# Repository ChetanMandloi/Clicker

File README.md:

# Clicker
PCB schematics, ESP code, User side programs for the clicker

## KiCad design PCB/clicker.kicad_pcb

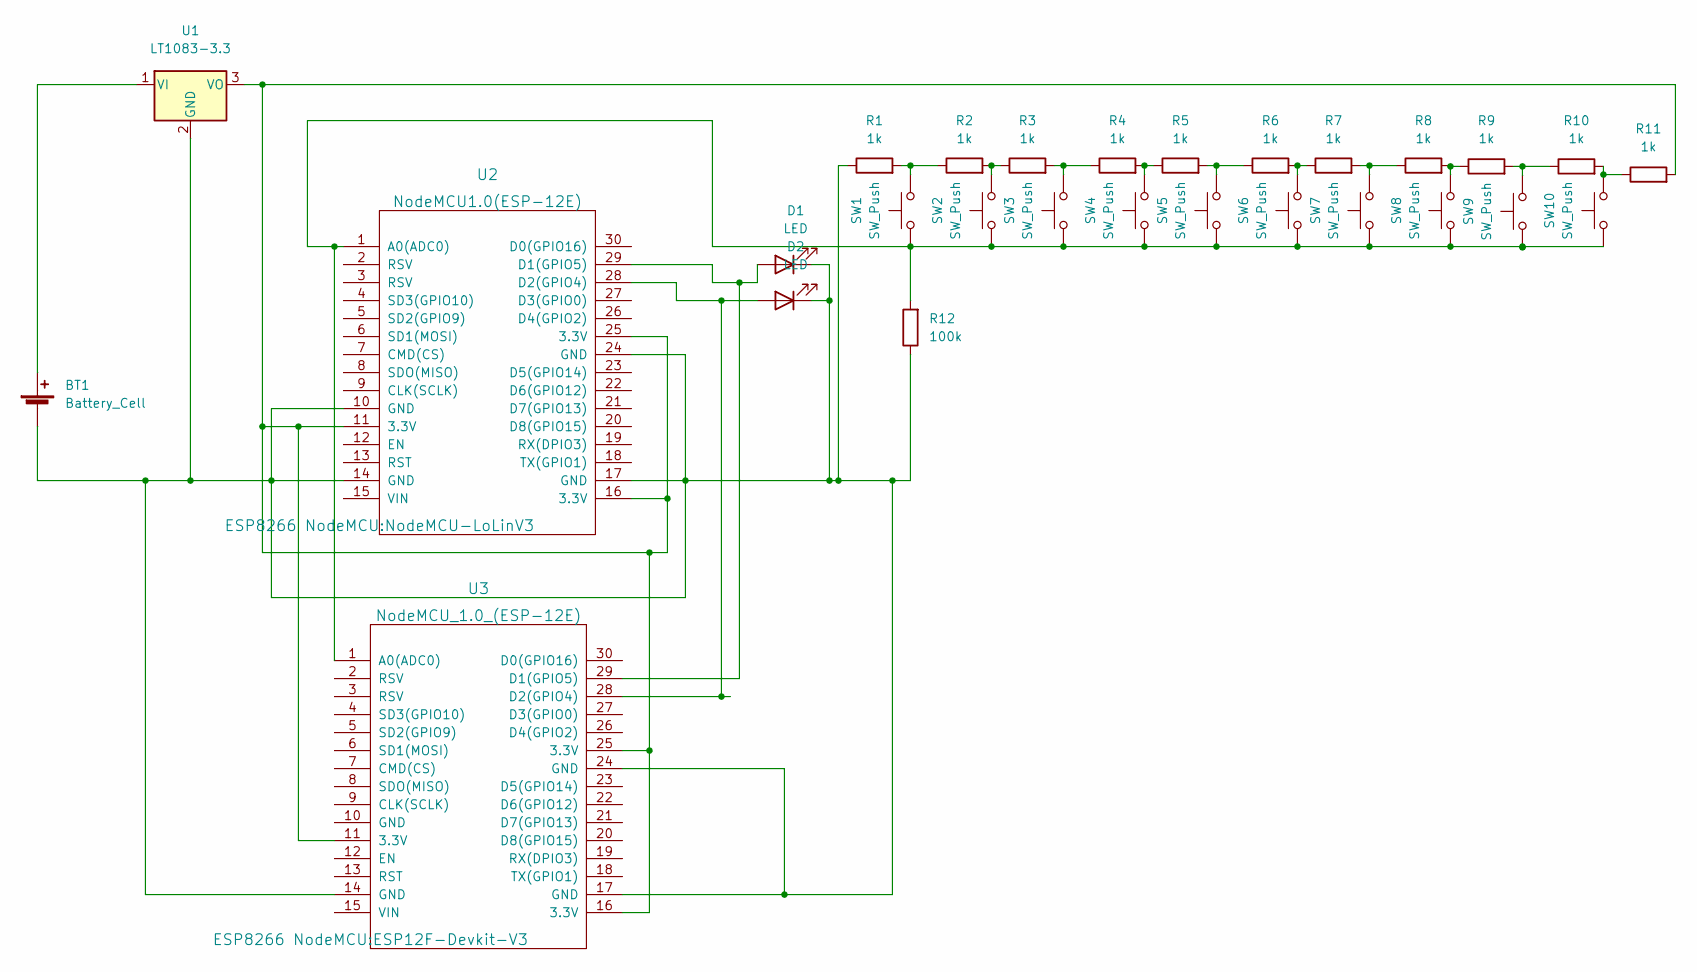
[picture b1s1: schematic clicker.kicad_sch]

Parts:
BT1: Battery_Cell; SolderWire-2.5sqmm_1x02_P7.2mm_D2.4mm_OD3.6mm
D1, D2: LED; LED_D3.0mm
R1, R2, R3, R4, R5, R6, R7, R8, R9, R10, R11: 1k; R_Axial_DIN0207_L6.3mm_D2.5mm_P10.16mm_Horizontal
R12: 100k; R_Axial_DIN0207_L6.3mm_D2.5mm_P10.16mm_Horizontal
SW1, SW2, SW3, SW4, SW5, SW6, SW7, SW8, SW9, SW10: SW_Push; SW_PUSH-12mm
U1: LT1083-3.3; SIP3_11.6x8.5mm
U2: NodeMCU1.0(ESP-12E); NodeMCU-LoLinV3
U3: NodeMCU_1.0_(ESP-12E); ESP12F-Devkit-V3

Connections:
unnamed: BT1.1 (+), U1.1 (VI)
unnamed: BT1.2 (-), D1.1 (K), D2.1 (K), R1.1, R12.1, U1.2 (GND), U2.10 (GND), U2.14 (GND), U2.17 (GND), U2.24 (GND), U3.14 (GND), U3.17 (GND), U3.24 (GND)
unnamed: D1.2 (A), U2.29 (D1(GPIO5)), U3.29 (D1(GPIO5))
unnamed: D2.2 (A), U2.28 (D2(GPIO4)), U3.28 (D2(GPIO4))
unnamed: R1.2, R2.1, SW1.2
unnamed: R2.2, R3.1, SW2.2
unnamed: R3.2, R4.1, SW3.2
unnamed: R4.2, R5.1, SW4.2
unnamed: R5.2, R6.1, SW5.2
unnamed: R6.2, R7.1, SW6.2
unnamed: R7.2, R8.1, SW7.2
unnamed: R8.2, R9.1, SW8.2
unnamed: R9.2, R10.1, SW9.2
unnamed: R10.2, R11.1, SW10.2
unnamed: R11.2, U1.3 (VO), U2.11 (3.3V), U2.16 (3.3V), U2.25 (3.3V), U3.11 (3.3V), U3.16 (3.3V), U3.25 (3.3V)
unnamed: R12.2, SW1.1, SW2.1, SW3.1, SW4.1, SW5.1, SW6.1, SW7.1, SW8.1, SW9.1, SW10.1, U2.1 (A0(ADC0)), U3.1 (A0(ADC0))

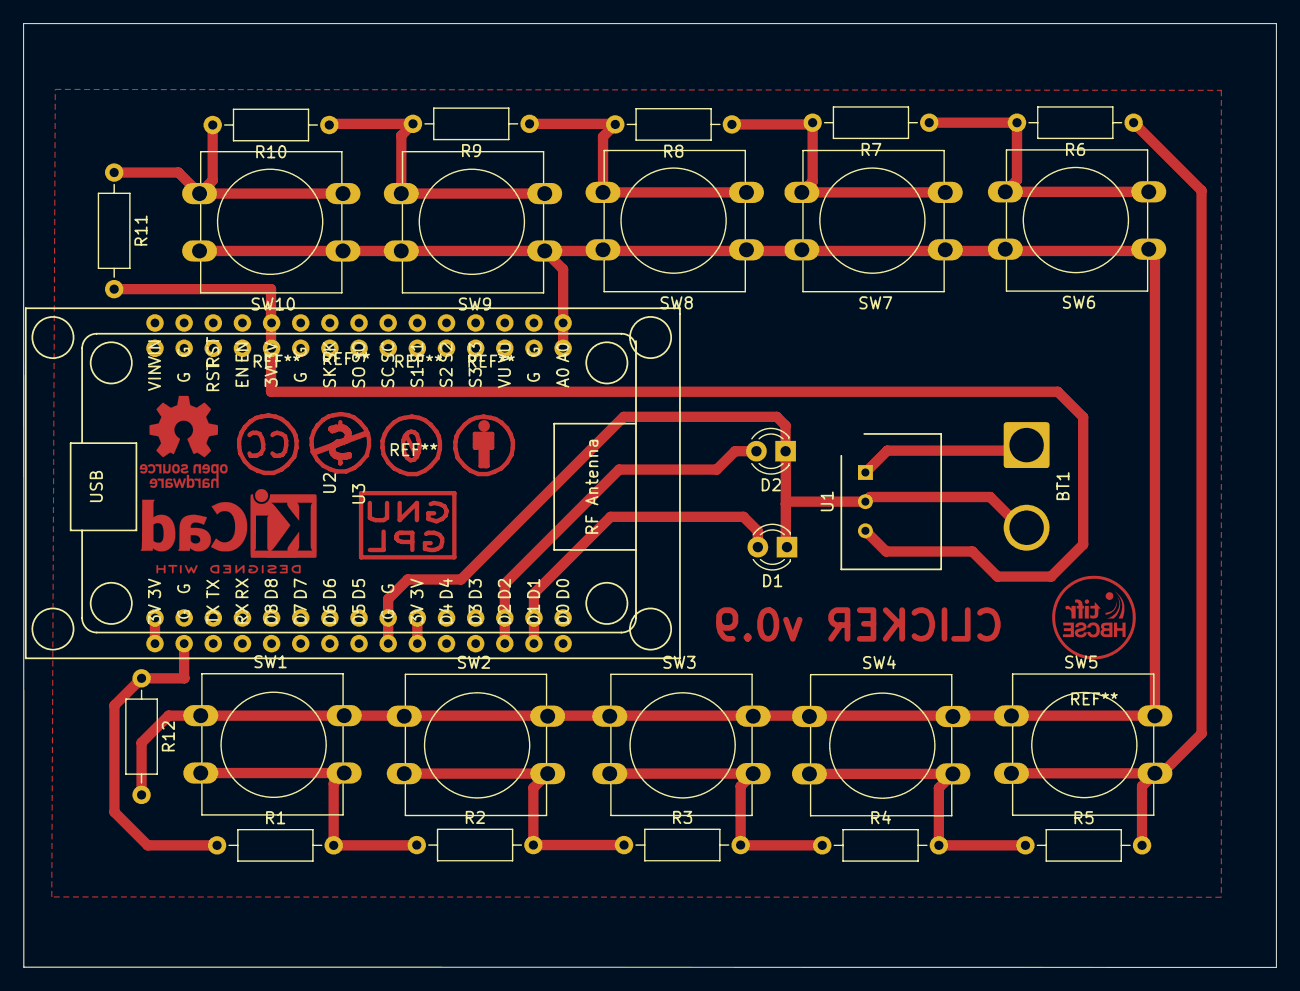
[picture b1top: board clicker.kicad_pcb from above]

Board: 2 copper layers, 109.2 x 82.2 mm, 28 parts (0 on the bottom side), 16 nets.

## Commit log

2023-02-17 PCB Schematics
2023-02-17 Pre GUI polling code
2023-02-17 Requirememt shuffle
2023-02-17 Initial Working Firmware
2023-06-04 Added reset feature
2023-06-05 Fixed debug adc value and removed mDNS
2023-06-07 Simultaneous polling and resseting, first gui
2023-06-08 Some documentation and some code cleanup
2023-06-10 more documentation and gui changes
2023-06-11 refactor
2023-06-11 Numbers of bar plots
2023-06-23 Label size and other minor tweak. new file for future scan update
2023-06-23 Timeouts changed
2023-08-08 update to thinkpad
